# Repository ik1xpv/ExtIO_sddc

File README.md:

## ExtIO_sddc.dll (software digital down converter) - Oscar Steila, ik1xpv

## Installation Instructions

You can download the latest EXTIO driver from the releases: https://github.com/ik1xpv/ExtIO_sddc/releases.
The direct link to the current version v1.2.0 Version released at 18/3/2021 is: https://github.com/ik1xpv/ExtIO_sddc/releases/download/v1.2.0/SDDC_EXTIO.ZIP.

*If you want to try the beta EXTIO driver which is for testing, you can find the binary for each change here: https://github.com/ik1xpv/ExtIO_sddc/actions. Select one specific code change you like to try, click on the link of the change. And you will find the binary on the bottom of the change.*

## Build Instructions for ExtIO

1. Install Visual Studio 2019 with Visual C++ support. You can use the free community version, which can be downloaded from: https://visualstudio.microsoft.com/downloads/
1. Install CMake 3.19+, https://cmake.org/download/
1. Running the following commands in the root folder of the cloned repro:

```bash
> mkdir build
> cd build
> cmake ..
> cmake --build .
or
> cmake --build . --config Release
> cmake --build . --config RelWithDebInfo
```

* You need to download **32bit version** of fftw library from fftw website http://www.fftw.org/install/windows.html. Copy libfftw3f-3.dll from the downloaded zip package to the same folder of extio DLL.

* If you are running **64bit** OS, you need to run the following different commands instead of "cmake .." based on your Visual Studio Version:
```
VS2022: >cmake .. -G "Visual Studio 17 2022" -A Win32
VS2019: >cmake .. -G "Visual Studio 16 2019" -A Win32
VS2017: >cmake .. -G "Visual Studio 15 2017 Win32"
VS2015: >cmake .. -G "Visual Studio 14 2015 Win32"
```

## Build Instructions for firmware

- download latest Cypress EZ-USB FX3 SDK from here: https://www.cypress.com/documentation/software-and-drivers/ez-usb-fx3-software-development-kit
- follow the installation instructions in the PDF document 'Getting Started with FX3 SDK'; on Windows the default installation path will be 'C:\Program Files (x86)\Cypress\EZ-USB FX3 SDK\1.3' (see pages 17-18) - on Linux the installation path could be something like '/opt/Cypress/cyfx3sdk'
- add the following environment variables:
```
export FX3FWROOT=<installation path>
export ARMGCC_INSTALL_PATH=<ARM GCC installation path>
export ARMGCC_VERSION=4.8.1
```
(on Linux you may want to add those variables to your '.bash_profile' or '.profile')
- all the previous steps need to be done only once (or when you want to upgrade the version of the Cypress EZ-USB FX3 SDK)
- to compile the firmware run:
```
cd SDDC_FX3
make
```

## Build Instruction for Linux

1. Install development packages:
```bash
> sudo apt install libfftw3-dev
```

1. Follow Windows Build Instruction to run cmake to build Linux libaray

## Directory structure:
    \Core\           > Core logic of the component
        r2iq.cpp			> The logic to demodulize IQ from ADC real samples
        FX3handler.cpp		> Interface with firmware
        RadioHandler.cpp    > The abstraction of different radios
        Radio\*.cpp         > Hardware specific logic
    \ExtIO_sddc\ 		> ExtIO_sddc sources,
        extio_sddc.cpp     > The implementation of EXTIO contract 
        tdialog.cpp			> The Configuration GUI Dialog
    \libsddc\        > libsddc lib
    \SDDC_FX3\          > Firmware sources

## Change Logs

### tag v1.4 version date 7/5/2024
- Add SoapySDR module for Linux & Windoes
- Embedded firmware into Core to avoid carrying firmware file.

Install SoapySDR on Linux via the follow command:
> export SOAPY_SDR_PLUGIN_PATH=<path of libSDDCSupport.so>

### tag  v1.3.0RC1 Version "V1.2 RC1" date 4/11/2021
- Use Ringbuffer for input and output #157
- Delegate the VHF and HF decision to radio class #194
- Debug trace via USB #195
- Arm neon port #203
- A dialogBox with SDR name and FX3 serial number allows selection of a device from many. #210

 So far the known issues:
- Al power up sometime FX3 is not enumerated as Cypress USB FX3 BootLoader Device. When it happens also Cypress USB Control Center app is not able to detect it and a hardware disconnect and reconnect maybe required to enumerate the unit.

### tag  v1.2.0 Version "V1.2.0" date 18/3/2021
- Fix the crosstalk HF <-> VHF/UHF issue #177
- When HDSDR's version >= HDSDR v2.81 beta3 (March 8, 2021) following an ADC's sampling rate change the new IF bandwidths are computed dynamically and restart of HDSDR in not required.

### tag  v1.2RC1 Version "V1.2 RC1" date 18/2/2021
- The ADC's nominal sampling frequency is user selectable from 50 MHz to 140 MHz at 1Hz step, 
- The reference calibration can be adjusted in the dialog GUI in a range of +/- 200 ppm. (#171)
- The tuner IF center frequency is moved to 4.570 MHz that is the standard for RT820T. We were using 5 MHz before when we did not have yet fine tune ability. (#159)
- Support for AVX/2/512 instructions added. This change may reduce CPU usage for some modern hardware.(#152) 
- The Kaiser-Bessel IF filter with 85% of Nyquist band are computed at initialization. It simplifies managment of IF filters (#147)
- Add automatically build verification for both master branch and PRs. This  feature of the Github environment speeds development checks(#141)

 So far the known issues:
- The ADC sampling frequency can be selected via the ExtIO dialog.  HDSDR versions <= 2.80 require to close HDSDR.exe and restart the application to have the right IF sample rates. Higher HDSDR releases will have dynamically allocated IF sample rates and they will not require the restart.
- This release does not operate correctly with HF103 and similar designs that do not use a pll to generate the ADC sampling clock.
- The accuracy is that of the SI5351a programming about 1 Hz

### tag  v1.1.0 Version "V1.1.0" date 29/12/2020
- Fix the round of rf/if gains in the UI #109
- Fix sounds like clipping, on strong stations #120
- Fix reboot of FX3 #119

 So far the known issues:
- The reference frequency correction via HDSDR -> Options -> Calibration Settings ->LO Frequency Calibration doesn't work correctly. This problem will be addressed in the next release.

### tag  v1.1RC1 Version "V1.1 RC1" date 20/12/2020
- Supports 128M ADC sampling rate selectable via the dialog GUI ( Justin Peng and Howard Su )
- Use of libsddc allows development of Linux support and Soapy integration ( Franco Venturi https://github.com/fventuri/libsdd) 
- Tune the LO with a 1Hz step everywhere (Hayati Ayguen https://github.com/hayguen/pffft).
- Move multi thread r2iq to a multithreaded pipeline model to better leverage multi cores. Remove callback in USB (adcsample) thread to HDSDR to make sure we can reach 128Msps.
- Continuous tuning LW,MW,HF and VHF.
- Dialog GUI has samplerates and gains settings for use with other SDR applications than HDSDR.
- Test harmonic R820T tuning is there (Hayati Ayguen https://github.com/librtlsdr/librtlsdr/tree/development)
- the gain correction is made via  HDSDR -> Options -> Calibration Settings ->S-Meter Calibration.

 So far the known issues:
- The reference frequency correction via HDSDR -> Options -> Calibration Settings ->LO Frequency Calibration doesn't work correctly. This problem will be addressed in the next release.
- The 128M adc rate is experimental and must be activated manually in the ExtIO dialog GUI. It works with RX888 hardware that have 60 MHz LPF and requires a quite fast PC.

### tag  v1.01 Version "V1.01 RC1" date 06/11/2020
- SDDC_FX3 directory contains ARM sources and GPIFII project to compile sddc_fx3.img
- Detects the HW type: BBRF103, BBRF103, RX888 at runtime.
- Si5351a and R820T2 driver moved to FX3 code
- Redesign of FX3 control commands
- Rename of FX3handler (ex: OpenFX3) and RadioHandler (ex: BBRF103) modules
- Simplified ExtIO GUI Antenna BiasT, Dither, and Rand.
- Reference frequency correction via software +/- 200 ppm range
- Gain adjust +/-20 dB step 1dB
- R820T2 controls RF gains via a single control from GUI
- ExtIO.dll designed for HDSDR use.
- HF103 added a tuning limit at ADC_FREQ/2.

### tag  v0.98  Version "SDDC-0.98" date  13/06/2019
   R820T2 is enabled to support VHF

### tag  v0.96  Version "SDDC-0.96" date  25/02/2018

### tag  v0.95  Version "SDDC-0.95" date 31/08/2017

Initial version

## References
- EXTIO Specification from http://www.sdradio.eu/weaksignals/bin/Winrad_Extio.pdf
- Discussion and Support https://groups.io/g/NextGenSDRs
- Recommended Application http://www.weaksignals.com/
- http://www.hdsdr.de
- http://booyasdr.sourceforge.net/
- http://www.cypress.com/

## Many thanks to
- Alberto di Bene, I2PHD
- Mario Taeubel
- LightCoder (aka LC)
- Howard Su
- Hayati Ayguen
- Franco Venturi
- All the Others !

#### 2016,2017,2018,2019,2020,2021  IK1XPV Oscar Steila - ik1xpv(at)gmail.com
https://sdr-prototypes.blogspot.com/

http://www.steila.com/blog

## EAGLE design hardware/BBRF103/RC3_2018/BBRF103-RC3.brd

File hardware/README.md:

## Hardware related documents

.Todo..

## Directory structure:
    \BBRF103\           
		RC1_2017\	> by Oscar Steila
		RC2_2018\	> by Oscar Steila
       	RC3_2018\	> by Radek Haša
		
	\RF103			> by Oscar Steila 
	
	\RX888			> by Justin Peng and Howard Su
	
	\Filters\
		2m_PBF_rev1.zip	> pcb gerbers see https://sdr-prototypes.blogspot.com/2021/03/filter-in-box.html

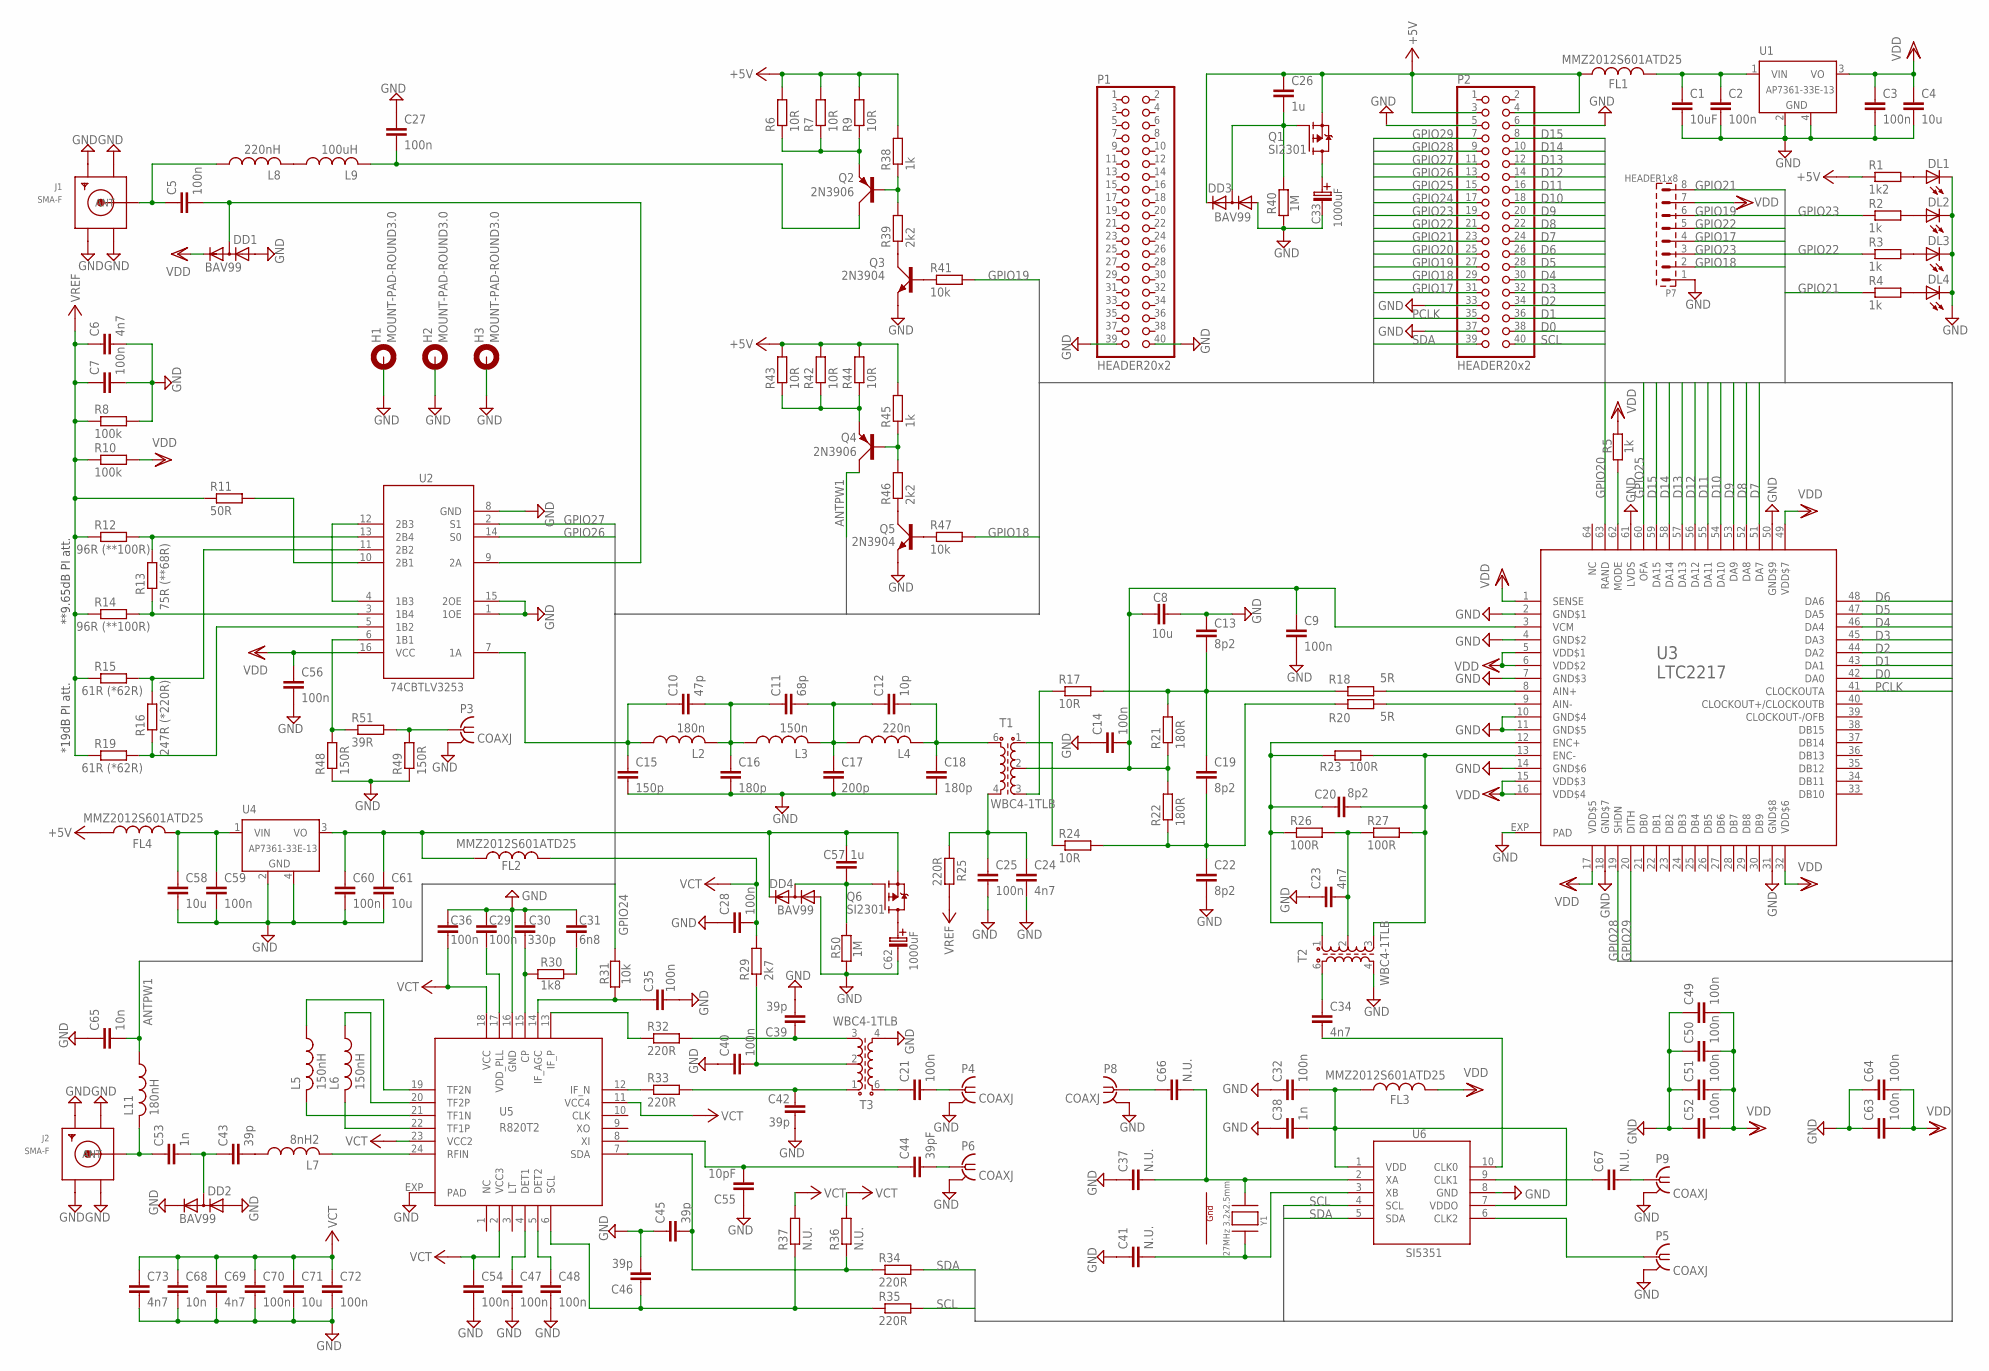
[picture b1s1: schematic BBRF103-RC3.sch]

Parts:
C1: 10uF; C0805K
C2, C3, C5, C7, C9, C14, C21, C25, C27, C28, C29, C32, C35, C36, C40, C47, C48, C49, C50, C51, C52, C54, C56, C59, C60, C63, C64, C70, C72: 100n; C0603K
C4, C58, C61, C71: 10u; C0805K
C6, C23, C24, C34, C69, C73: 4n7; C0603K
C8: 10u; C0603K
C10: 47p; C0603K
C11: 68p; C0603K
C12: 10p; C0603K
C13, C19, C20, C22: 8p2; C0603K
C15: 150p; C0603K
C16, C18: 180p; C0603K
C17: 200p; C0603K
C26, C57: 1u; C0603K
C30: 330p; C0603K
C31: 6n8; C0603K
C33, C62: 1000uF; C_EL_5
C37, C41, C66, C67: N.U.; C0603K
C38, C53: 1n; C0603K
C39, C42, C43, C45, C46: 39p; C0603K
C44: 39pF; C0603K
C55: 10pF; C0603K
C65, C68: 10n; C0603K
DD1, DD2, DD3, DD4: BAV99; SOT23
DL1, DL2, DL3, DL4: LEDCHIPLED_0805; CHIPLED_0805
FL1, FL2, FL3, FL4: MMZ2012S601ATD25; L2012C
H1, H2, H3: MOUNT-PAD-ROUND3.0; 3,0-PAD
J1, J2: SMA-F; SMA_EDGELAUNCH
L2: 180n; L2012C
L3: 150n; L2012C
L4: 220n; L2012C
L5, L6: 150nH; C0603K
L7: 8nH2; C0603K
L8: 220nH; L2012C
L9: 100uH; L2012C
L11: 180nH; C0603K
P1, P2: HEADER20x2; 2X20
P3, P4, P5, P6, P8, P9: COAXJ
P7: HEADER1x8; S1G8_JUM
Q1, Q6: SI2301; SOT23
Q2, Q4: 2N3906; SOT23W_INFINEON
Q3, Q5: 2N3904; SOT23W_INFINEON
R1: 1k2; R0603
R2, R3, R4, R5, R38, R45: 1k; R0603
R6, R7, R9, R17, R24, R42, R43, R44: 10R; R0603
R8, R10: 100k; R0603
R11: 50R; R0603
R12, R14: 96R (**100R); R0603
R13: 75R (**68R); R0603
R15, R19: 61R (*62R); R0603
R16: 247R (*220R); R0603
R18, R20: 5R; R0603
R21, R22: 180R; R0603
R23, R26, R27: 100R; R0603
R25, R32, R33, R34, R35: 220R; R0603
R29: 2k7; R0603
R30: 1k8; R0603
R31, R41, R47: 10k; R0603
R36, R37: N.U.; R0603
R39, R46: 2k2; R0603
R40, R50: 1M; R0603
R48, R49: 150R; R0603
R51: 39R; R0603
T1, T2, T3: WBC4-1TLB; WBC4-1WL
U1, U4: AP7361-33E-13; SOT223
U2: 74CBTLV3253; TSSOP16
U3: LTC2217; QFN64-9X9
U5: R820T2; QFN24
U6: SI5351; MSOP10
Y1: 27MHz 3.2x2.5mm; NX3225

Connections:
+5V: C26.1, DD3.2 (C), FL1.1, FL4.1, P2.3, P2.4, Q1.2 (S), R1.1, R6.2, R7.2, R9.2, R38.2, R42.2, R43.2, R44.2, R45.2
ANTPW1: C65.2, L11.1, Q4.3 (C)
D0: P2.38, U3.42 (DA0)
D1: P2.36, U3.43 (DA1)
D2: P2.34, U3.44 (DA2)
D3: P2.32, U3.45 (DA3)
D4: P2.30, U3.46 (DA4)
D5: P2.28, U3.47 (DA5)
D6: P2.26, U3.48 (DA6)
D7: P2.24, U3.51 (DA7)
D8: P2.22, U3.52 (DA8)
D9: P2.20, U3.53 (DA9)
D10: P2.18, U3.54 (DA10)
D11: P2.16, U3.55 (DA11)
D12: P2.14, U3.56 (DA12)
D13: P2.12, U3.57 (DA13)
D14: P2.10, U3.58 (DA14)
D15: P2.8, U3.59 (DA15)
G1: Y1.4 (G1)
G2: Y1.2 (G2)
GND: C1.2, C2.2, C3.2, C4.2, C6.2, C7.2, C8.2, C9.2, C13.1, C14.1, C15.2, C16.2, C17.2, C18.2, C22.2, C23.1, C24.2, C25.2, C27.1, C28.1, C29.1, C30.1, C31.1, C32.1, C33.C- (C_EL-), C35.2, C36.1, C37.1, C38.1, C39.2, C40.1, C41.1, C42.1, C45.1, C46.2, C47.2, C48.2, C49.1, C50.1, C51.1, C52.1, C54.2, C55.1, C56.2, C58.2, C59.2, C60.2, C61.2, C62.C- (C_EL-), C63.1, C64.1, C65.1, C68.2, C69.2, C70.2, C71.2, C72.2, C73.2, DD1.1 (A), DD2.1 (A), DD2.2 (C), DD3.1 (A), DD4.1 (A), DL1.C, DL2.C, DL3.C, DL4.C, H1.B3,0, H2.B3,0, H3.B3,0, J1.GND@1 (GND4), J1.GND@2 (GND3), J1.GND@3 (GND2), J1.GND@4 (GND1), J2.GND@1 (GND4), J2.GND@2 (GND3), J2.GND@3 (GND2), J2.GND@4 (GND1), P1.39, P1.40, P2.5, P2.6, P2.33, P2.37, P3.2 (GND), P4.2 (GND), P5.2 (GND), P6.2 (GND), P7.1, P8.2 (GND), P9.2 (GND), Q3.2 (E), Q5.2 (E), R8.2, R40.1, R48.1, R49.1, R50.1, T2.4, T3.4, U1.2 (GND), U1.4 (GND), U2.1 (1OE), U2.8 (GND), U2.15 (2OE), U3.2 (GND$1), U3.4 (GND$2), U3.7 (GND$3), U3.10 (GND$4), U3.11 (GND$5), U3.14 (GND$6), U3.18 (GND$7), U3.31 (GND$8), U3.50 (GND$9), U3.61 (LVDS), U3.EXP (PAD), U4.2 (GND), U4.4 (GND), U5.16 (GND), U5.EXP (PAD), U6.8 (GND)
GPIO17: P2.31, P7.4
GPIO18: P2.29, P7.2, R47.2
GPIO19: P2.27, P7.6, R41.2
GPIO20: P2.25, U3.63 (RAND)
GPIO21: P2.23, P7.8, R4.1
GPIO22: P2.21, P7.5, R3.1
GPIO23: P2.19, P7.3, R2.1
GPIO24: P2.17, R31.2
GPIO25: P2.15, U3.60 (OFA)
GPIO26: P2.13, U2.14 (S0)
GPIO27: P2.11, U2.2 (S1)
GPIO28: P2.9, U3.19 (SHDN)
GPIO29: P2.7, U3.20 (DITH)
unnamed: DL1.A, R1.2
unnamed: C33.C+ (C_EL+), Q1.3 (D)
unnamed: C26.2, DD3.3 (AC), Q1.1 (G), R40.2
unnamed: DL2.A, R2.2
unnamed: DL3.A, R3.2
unnamed: DL4.A, R4.2
unnamed: R5.1, U3.62 (MODE)
unnamed: C20.2, R23.2, R27.2, T2.3, U3.13 (ENC-)
unnamed: C1.1, C2.1, FL1.2, U1.1 (VIN)
unnamed: C23.2, R26.2, R27.1, T2.2
unnamed: C20.1, R23.1, R26.1, T2.1, U3.12 (ENC+)
unnamed: C34.1, T2.6
unnamed: C34.2, U6.10 (CLK0)
unnamed: C37.2, C66.2, U6.2 (XA), Y1.1 (X1)
unnamed: C67.2, P9.1
unnamed: C66.1, P8.1
unnamed: C32.2, C38.2, FL3.1, U6.1 (VDD), U6.7 (VDDO)
unnamed: C67.1, U6.9 (CLK1)
unnamed: P5.1, U6.6 (CLK2)
unnamed: R20.2, U3.9 (AIN-)
unnamed: R18.2, U3.8 (AIN+)
unnamed: C41.2, U6.3 (XB), Y1.3 (X2)
unnamed: C13.2, C19.1, R17.2, R18.1, R21.2
unnamed: C8.1, C9.1, C14.2, R21.1, R22.2, T1.2, U3.3 (VCM)
unnamed: C19.2, C22.1, R20.1, R22.1, R24.2
unnamed: R24.1, T1.1
unnamed: R17.1, T1.3
unnamed: C24.1, C25.1, R25.1, T1.4
unnamed: C12.2, C18.1, L4.2, T1.6
unnamed: C11.2, C12.1, C17.1, L3.2, L4.1
unnamed: C10.2, C11.1, C16.1, L2.2, L3.1
unnamed: C10.1, C15.1, L2.1, U2.7 (1A)
unnamed: C62.C+ (C_EL+), Q6.3 (D)
unnamed: Q3.1 (B), R41.1
unnamed: Q3.3 (C), R39.1
unnamed: Q2.1 (B), R38.1, R39.2
unnamed: C58.1, C59.1, FL4.2, U4.1 (VIN)
unnamed: C57.2, DD4.3 (AC), Q6.1 (G), R50.2
unnamed: Q2.2 (E), R6.1, R7.1, R9.1
unnamed: C48.1, U5.5 (DET2)
unnamed: C45.2, R34.1, R36.1, U5.7 (SDA)
unnamed: Q5.1 (B), R47.1
unnamed: Q5.3 (C), R46.1
unnamed: Q4.1 (B), R45.1, R46.2
unnamed: Q4.2 (E), R42.1, R43.1, R44.1
unnamed: C47.1, U5.4 (DET1)
unnamed: C21.1, T3.6
unnamed: C21.2, P4.1
unnamed: C42.2, R33.2, T3.1
unnamed: C39.1, R32.2, T3.3
unnamed: C40.2, R29.1, T3.2
unnamed: R48.2, R51.1, U2.6 (1B1)
unnamed: R33.1, U5.12 (IF_N)
unnamed: C44.2, P6.1
unnamed: C44.1, C55.2, U5.8 (XI)
unnamed: C46.1, R35.1, R37.1, U5.6 (SCL)
unnamed: P3.1, R49.2, R51.2
unnamed: R32.1, U5.13 (IF_P)
unnamed: C35.1, R31.1, U5.14 (IF_AGC)
unnamed: C30.2, R30.1, U5.15 (CP)
unnamed: C31.2, R30.2
unnamed: C27.2, L9.2, Q2.3 (C)
unnamed: C29.2, U5.17 (VDD_PLL)
unnamed: C5.2, DD1.3 (AC), U2.9 (2A)
unnamed: L8.2, L9.1
unnamed: L6.2, U5.22 (TF1P)
unnamed: L6.1, U5.20 (TF2P)
unnamed: L5.2, U5.21 (TF1N)
unnamed: L5.1, U5.19 (TF2N)
unnamed: L7.2, U5.24 (RFIN)
unnamed: C43.2, L7.1
unnamed: C43.1, C53.2, DD2.3 (AC)
unnamed: C5.1, J1.P (ANT), L8.1
unnamed: C53.1, J2.P (ANT), L11.2
unnamed: R12.2, R13.2, U2.13 (2B4)
unnamed: C57.1, C60.1, C61.1, DD4.2 (C), FL2.1, Q6.2 (S), U4.3 (VO)
unnamed: R13.1, R14.2, U2.3 (1B4)
unnamed: R15.2, R16.2, U2.11 (2B2)
unnamed: R16.1, R19.2, U2.5 (1B2)
unnamed: U2.4 (1B3), U2.12 (2B3)
unnamed: R11.2, U2.10 (2B1)
PCLK: P2.35, U3.41 (CLOCKOUTA)
SCL: P2.40, R35.2, U6.4 (SCL)
SDA: P2.39, R34.2, U6.5 (SDA)
VCT: C28.2, C36.2, C54.1, C68.1, C69.1, C70.1, C71.1, C72.1, C73.1, FL2.2, R29.2, R36.2, R37.2, U5.2 (VCC3), U5.11 (VCC4), U5.18 (VCC), U5.23 (VCC2)
VDD: C3.1, C4.1, C49.2, C50.2, C51.2, C52.2, C56.1, C63.2, C64.2, DD1.2 (C), FL3.2, P7.7, R5.2, R10.2, U1.3 (VO), U2.16 (VCC), U3.1 (SENSE), U3.5 (VDD$1), U3.6 (VDD$2), U3.15 (VDD$3), U3.16 (VDD$4), U3.17 (VDD$5), U3.32 (VDD$6), U3.49 (VDD$7)
VREF: C6.1, C7.1, R8.1, R10.1, R11.1, R12.1, R14.1, R15.1, R19.1, R25.2

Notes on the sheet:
*19dB PI att.
**9.65dB PI att.

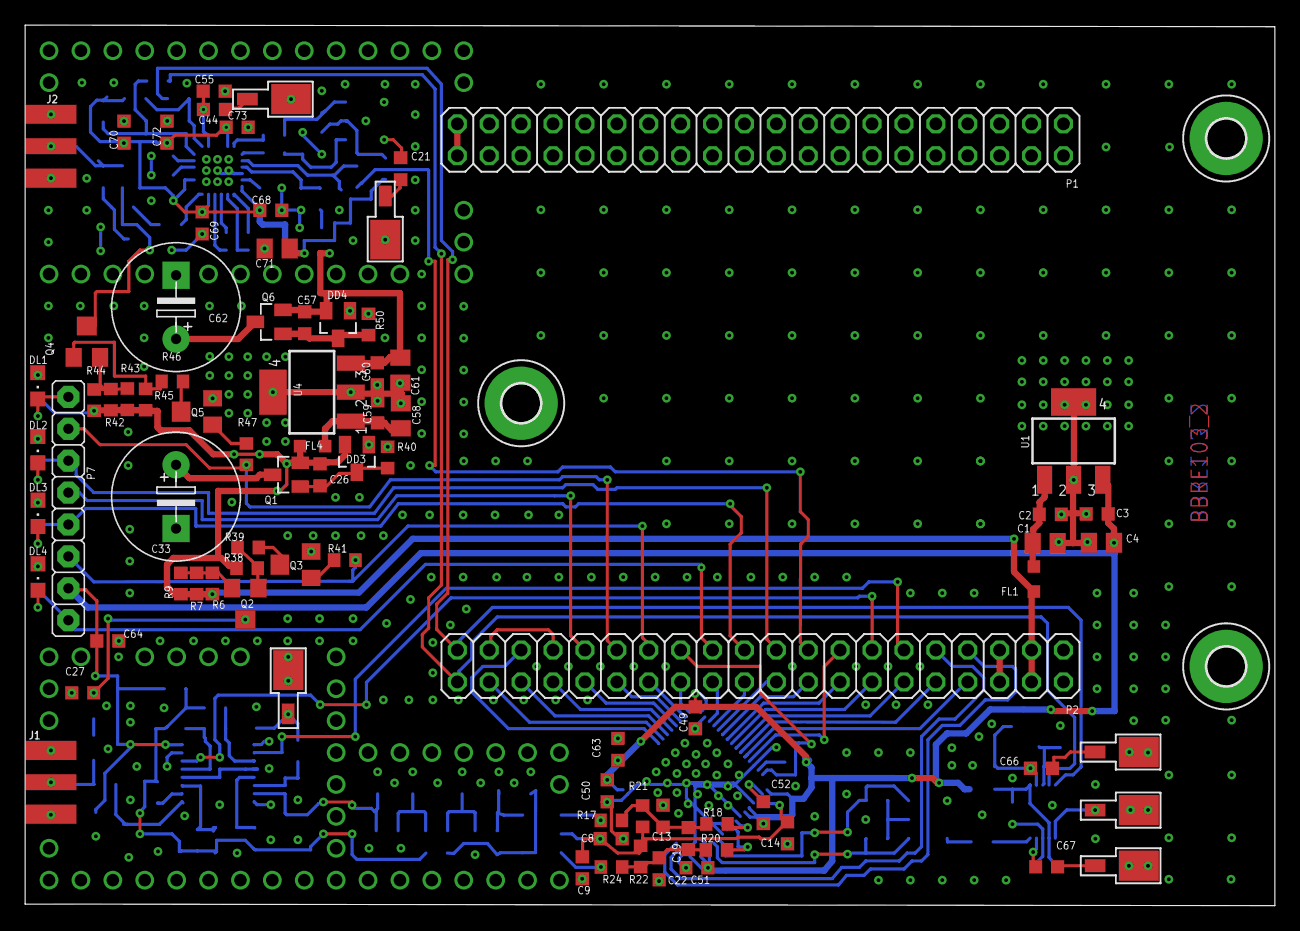
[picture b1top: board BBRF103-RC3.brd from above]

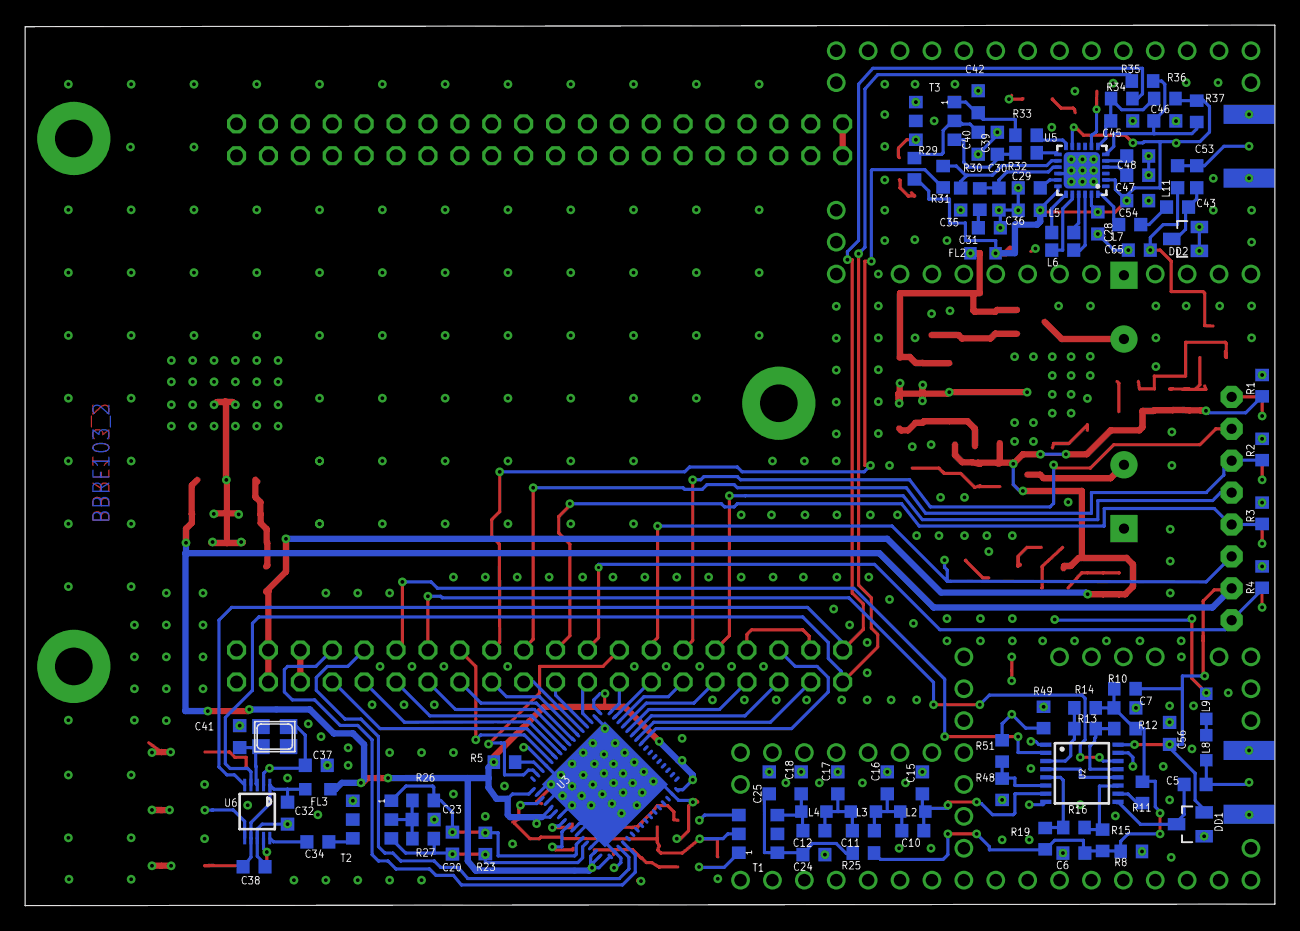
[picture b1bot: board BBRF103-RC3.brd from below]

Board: 2 copper layers, 99.5 x 70.1 mm, 174 parts (88 on the bottom side), 119 nets.

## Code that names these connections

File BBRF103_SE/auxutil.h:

#ifndef _INCLUDED_AUXUTIL_H_
#define _INCLUDED_AUXUTIL_H_

#include "cyu3externcstart.h"
//#include "cyu3types.h"
#include "cyu3usbconst.h"
#include "cyu3usb.h"

#define LED_OVERLOAD (21)
#define LED_MODEA    (22)
#define LED_MODEB    (23)
// redefine to error handler
#define GPIO_LED1   (21)
#define GPIO_LED2   (22)
#define GPIO_LED3   (23)
#define LED_ON (1)
#define LED_OFF (0)
#define ERR_DIGIT_ON	100
#define ERR_DIGIT_OFF	400
#define ERR_DIGIT_SPACE	250
#define ERR_DIGIT_END   750

#define OUTXIO0 (1) 	// LED_OVERLOAD  GPIO21  bit position
#define OUTXIO1 (2) 	// LED_MODEA  GPIO22
#define OUTXIO2 (4) 	// LED_MODEB  GPIO22

#define OUTXIO3 (8)  	// SEL0  GPIO26
#define OUTXIO4 (16) 	// SEL1  GPIO27

#define OUTXIO5 (32)  	// SHDWN  GPIO28
#define OUTXIO6 (64)  	// DITH   GPIO29
#define OUTXIO7 (128)  	// DITH   GPIO20

typedef struct outxio_t
{
    uint8_t  buffer[4];         /* The actual byte used is [0]  */
} outxio_t;

typedef struct i2cxio_t
{
    uint8_t  i2caddr;            /* The i2c device address  */
    uint8_t  regaddr;            /* The device register address  */
    uint8_t  isRead;           	 /* (0) False value WRITE, (1) True value Read */
    uint8_t  lencount;			 /*	 byte count  < 12 */
    uint8_t  databyte[12];
} i2cxio_t;


#define CY_FX_RQT_I2C_WRITE                     (0xBA)
#define CY_FX_RQT_I2C_READ                      (0xBE)
#define CY_FX_RQT_GPIO_WRITE 					(0xBC)
#define CY_FX_RQT_GPIO_PWM                      (0xBD)
#define CY_FX_RQT_RESET                      	(0xCC)
#define CY_FX_RQT_START                      	(0xAA)
#define CY_FX_RQT_STOP                      	(0xBB)

void CyFxAppErrorHandler (  CyU3PReturnStatus_t apiRetStatus );
CyBool_t CyFxApplnLPMRqtCB ( CyU3PUsbLinkPowerMode link_mode);
void CyFxSlFifoApplnDebugInit (void);
void setDescriptors(void);
void SDR_ErrorHandler( CyU3PReturnStatus_t apiRetStatus, int code );
#endif

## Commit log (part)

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2021-03-17 Fix cross lock issue (#183)
    * Always stop r820 no matter if init is done
    * Add delay before checking PLL lock state
2021-03-17 New way to upload artifact
2021-03-17 New way to upload artifact (#184)
2021-03-18 restructure the source code
2021-03-18 Add FX3 SDK
2021-03-18 Add action support to build firmware
2021-03-18 Use the proper config
2021-03-18 seperate the firmware build
2021-03-18 fix build again
2021-03-18 Move declare to header file
2021-03-18 use firmware from linux build
2021-03-18 fix the build type constant
2021-03-18 v1.2.0 candidate (#185)
    Label v1.2.0 change
2021-03-18 Update RadioHandler.cpp
    VHF tuning sign of correction fixed
2021-03-18 Update RadioHandler.cpp (#186)
    VHF tuning sign of correction fixed
2021-03-19 Reduce cross talk from HF->VHF (#187)
2021-03-22 Update RX888R2Radio.cpp (#189)
2021-03-22 serial trace fix 4
2021-03-23 serial trace fix 4 (#190)
    * serial trace fix 4
    * layout fix
2021-03-25 Add libusb support
2021-03-27 Update README.md (#192)
2021-04-04 RXLUCY fix 2
2021-04-11 Fix build on OSX
2021-04-11 Move rf mode switching into hardware
2021-04-11 normalize tuner interface
2021-04-11 Cleanup ad5815 driver
2021-04-11 Add FM Notch
2021-04-11 Add prototype
2021-04-11 update rx888r3
2021-04-11 Fix linux build
2021-04-12 Add undersampling support
2021-04-12 Fix tune logic
2021-04-13 Fix tuner
2021-04-13 Debug trace FX3 via USB
2021-04-14 Reload FX3 linuxFix
2021-04-14 Debug trace FX3 via USB (#195)
    * Debug trace FX3 via USB
    * Reload FX3 linuxFix
    * linux fix tentative 2
2021-04-14 Update driver
2021-04-14 Fix gpio set for rx888r3
2021-04-15 Move to IF=20M
2021-04-15 Fix a number typo
2021-04-17 fix step 3
2021-04-18 Lower the switch point to 220M
2021-04-19 selection USB UART console
    define _DEBUG_USB_ in Interface.h
    ifdef USB <-> ExtIO dialog console
    else UART <-> serial terminal
2021-04-19 command list fix
2021-04-19 maxlen fix
    MAXLEN_D_USB is defined in Interface,h
2021-04-20 Move rf mode switching into hardware (#194)
    Delegate the VHF and HF decision to radio class.
    Normalize Tuner logic inside firmware. No matter what tuner is used, the interface kept same.
    add rx888mk3 prototype code.
2021-04-20 Update to 194
    _DEBUG flag is commented in config,h
    defined in project configuration debug
    In rd5815 is used DebugPrinf that can be definad as USB or serial in Application.h
2021-04-20 Console input2 fx3 (#197)
    * fix step 3
    * selection USB UART console
    define _DEBUG_USB_ in Interface.h
    ifdef USB <-> ExtIO dialog console
    else UART <-> serial terminal
    * fix Enter command
2021-04-24 GPIO50 pd BBRF103 (#198)
    BBRF103 detects pull down at GPIO50
2021-04-26 Remove inputbuffer parameter
2021-04-26 Move out simd related functions to simd.h
2021-04-26 Move plan_f2t out of thread context
2021-04-26 reduce spin count to 100
2021-04-27 Use Ringbuffer for Input&output Buffer (#157)
    * use Ringbuffer for input and output
    * Still use fixed EXT_BLOCKLEN
    * Fix Linux build
    * Fix linux build
    * reduce spin count to 100
2021-04-27 reformat the code a bit
2021-04-29 fix noise issue
2021-04-30 Create ifft plan once
2021-04-30 Support more decimate rates
2021-05-06 Use Start function to pass adcrate
2021-05-06 fix tune frequency logic
2021-05-06 Fix test case
2021-05-06 Fix libsddc on new API
2021-05-06 Get ExtIO works under new code
2021-05-06 Add back the support to save samples
2021-05-10 EXT_BLOCKLEN is parameter of freq2iq.
2021-05-10 Add back the debug and stats support
2021-05-10 Move intitialize to constructor
2021-05-10 remove debug code
2021-05-11 Add new interface to get uniqe serial number
2021-05-14 Cleanup the code
2021-05-28 Fix the size issue for ringbuffer
2021-07-15 Dynamic detection of NEON from hardware
2021-07-15 Compiles and passes unit tests on ARMv7 (OrangePi)
2021-07-15 X86_64 testing, portable printf format
2021-07-15 Return to 1 second run time for R2IQ tests
2021-09-29 Arm neon port (#203)
    * Compiles and passes unit tests on ARMv7 (OrangePi)
    * Dynamic detection of NEON from hardware
    * Rate limit hardware emulator, print counters
    * X86_64 testing, portable printf format
    * Return to 1 second run time for R2IQ tests
    * Remove wisdom files, align printf
2021-09-29 Detect RX888 more reliable (#204)
2021-10-24 two devices manual selection
    If the fx3handler::GetFx3Device() finds two devices a msgBox at run time asks witch one use.
    It's a rude solution , a better one with the use of SN to identify the device is planned in future
2021-10-27 Update FX3handler.cpp
    Message Box label
2021-10-29 Wait after firmware change
    If the device at power up is detected as Cypress FX3 Bootloader device,
    the added wait gives more time to enumering as StreamerExample device
2021-11-03 Select dialogbox
    In ExtIO_sddc,cpp InitHW() opens dialogBox to select a device when there are many FX3 devices.
2021-11-03 Linux build patch
    TODO
2021-11-03 linux buils hoops
2021-11-04 Ver 1.3.0 RC1 FW 2.02
    SWVERSION 1.3.0 RC1
    Firmware 2.02
2021-11-04 two devices manual selection (#210)
    * in the USBdescriptor of FX3 the serial number has been added ( thanks to Franco ideas and code )
    * Ver 1.3.0 RC1 FW 2.02
    ExtIO_sddc enumerates all the Cypress FX3 connected devices.
    A dialogBox ask to select one of many if required.
2021-11-16 Fix the logic to detect HDSDR
2021-12-10 BBRF103 documentation update
    Old Posts added in \hardware\BBRF103
2021-12-12 Add logic to persistent settings in non-HDSDR (#205)
    * Add logic to persistent settings in non-HDSDR
    * Fix the logic to detect HDSDR
2022-03-08 Use windows-2019
    windows-latest doesn't carry vs2019
2022-03-08 Use windows-2019 (#215)
    windows-latest doesn't carry vs2019
2022-04-02 Fix for systems that do not support usbfs zerocopy feature.
2022-04-02 Fix compiler error with clang
2022-04-02 Fix compile error
2022-04-03 Improve internal API (#218)
    * Improve internal API
    * Fix Linux build
2022-04-11 Support multi channels in dsp
2022-04-13 Add hermeslite emu
2022-04-13 cleanup code
2022-04-13 Fix bug in multi channel
2022-05-08 Fix freq shift
2022-05-08 ringbuffer add timeout to prevent hang forever
2022-05-09 Support multi devices
2022-05-09 Cleanup
2022-05-10 Add const modifier to firmware array
    As the firmware BLOB is not expected to be changed during downloading to
    a device.
2022-05-10 another try to fix windows build
2022-05-10 Add const modifier to firmware array (#224)
    As the firmware BLOB is not expected to be changed during downloading to
    a device.
2022-05-10 Make it work under linux with gqrx/gr-osmosdr
    Requires patched gr-osmosdr (gr3.7 only so far)
    https://github.com/vladisslav2011/gr-osmosdr/tree/ngrx
    No correct device listing and sample rates list.
    Gain selection is still a bit buggy.
    Fix test segfault.
    Do not delete fx3Handler as RadioHandlerClass::~RadioHandlerClass()
2022-05-10 Upload new firmware
2022-05-10 Improve compatibility with intel hubs (#225)
    Disable LPM while streaming to prevent dropouts.
2022-05-10 One more place to use const for firmware binary (#226)
2022-05-11 Use sampling rate of 96M
2022-05-15 define ht lenght
    #define HTLEN in fft_mt_r2iq.cpp allows manual test other lenght
2022-05-16 HTLEN
    #define HTLEN in config.h
2022-05-21 Soft tone generator
    #define _SOFT_TONE_DEBUG in config.h
    enables the generation of soft tone
    close to 1MHz with ADC clk 64MHz,
    the tone period is an integer factor of transferSamples.
    GUI Rand CheckBox activates the software generated tone.
2022-05-23 Update config.h
    SWVERSION 1.3.3.Alfa
2022-06-09 large FFTN test
    Test in config,c FFTN_R_ADC (32768)
    htlen => 12289
2022-09-03 Include git version tag into the version number
2022-09-03 Add dev index to open API of core
2022-09-03 Embed firmware file into libsddc
2022-09-05 Add error codes
2022-09-05 Cleanup CMakeLists.txt
2022-09-05 Include git version tag into the version number (#228)
2023-10-29 Do not build linux support on windows machine
2023-10-30 Start refactoring to add libusb support in windows
2023-10-30 Save wip
2023-10-31 Fix some some msvc compile warnings
2023-11-02 Refactor large part of code and dir structures
2023-11-02 Fix CyAPI support build
2023-11-02 Try to fix libusb support build
2023-11-02 Fix optimisation warnings
2023-11-02 Use safe functions and fix some warnings
2023-11-03 Fix libusb include error
2023-11-03 Fix libusb include on macOS
2023-11-04 Windows : Integrate CyAPI and libusb support in one static libUsb library
2023-11-04 Fix build in windows
2023-11-05 Fix unit tests build
2023-11-06 Refactor more wip
2023-11-06 Fix unittest build on windows
2023-11-08 Cmake : Clean some lines
2023-11-10 Convert a function that translates wide characters to multibyte characters from Windows-specific code to multiplatform code
2023-11-26 Fix compiling in mingw64
2023-11-30 Try to fix build in mingw64
2023-12-03 fix macos build
2023-12-06 Fix parallel build
2023-12-07 Clean
2023-12-07 Clean code
2023-12-19 Spectrum works in gqrx
2023-12-22 Fix build in mingw
2023-12-24 Use CyAPI driver by default
2023-12-25 Soapy : Add getFrequency method
2023-12-25 Some progression in frequency control
2023-12-29 Fix build in linux
2024-01-04 Fix build on ubuntu 18.04
2024-01-07 Fix unittest
2024-01-09 Fix firmware build
2024-01-11 Fix firmware build (#232)
2024-01-11 Fix linux build for UT (#233)
2024-01-14 Fix SoapySDRUtil --probe command
2024-01-14 Fix some memory leaks
2024-07-03 getName is a const function
2024-07-03 Add prefix to debug output
2024-07-04 initialize block_size
2024-07-04 add debug options
2024-07-04 SOAPYSDR lib works
2024-07-05 revert the change to clearnup transfer
2024-07-06 Fix usb handling
2024-07-06 更新 FX3handler.cpp
    fix windows build
2024-07-06 Add frequency list
2024-07-06 Support Gain modes
2024-07-06 Unroll some tight loops
2024-07-06 Fix UT
2024-07-08 cleanup cmakefiles
2024-07-08 Fix compile under x64
2024-07-08 frequency is uint64
2024-07-09 Fix USB Crash
    developed by Franco VENTURI
2024-07-09 Fix github action to add 64bit build and soapy build
2024-07-12 Update vcpkg
2024-07-12 Use vcpkg for win64 build
2024-07-12 add SoapySDR Lib (#234)
    * getName is a const function
    * Add prefix to debug output
    * Add SoapySDR lib named sddc
    * initialize block_size
    * add debug options
    * SOAPYSDR lib works
2024-07-19 Make streaming work in macos(intel)
2024-07-19 Fix hang issue when stopping stream
2024-08-24 Github actions: Add macos CI
2025-04-16 Allow toggle bias-t in SoapySDDC
2025-04-26 check boolen value safer
2025-04-26 Allow toggle bias-t in SoapySDDC (#237)
    * Allow toggle bias-t in SoapySDDC
    * check boolen value safer
2025-04-26 Fix unittest compile failure
2025-11-01 Fix os
2025-11-01 Fix macos build for arm64
2025-11-01 Update filename
2025-11-01 Update vs version
2025-11-01 Update file upload path
2026-02-10 Fix frequency offset bug at 32MHz sample rate
    Remove hardcoded 8MHz offset in getFrequency() when sampleRate is 32MHz.
    This offset caused spectrum display to start at 8MHz instead of 0Hz,
    leaving 0-8MHz range empty.
    The bug existed since the initial SoapySDR implementation.
2026-02-11 Fix CI build: add apt-get update before package installation
2026-02-11 Fix PR #240 AI review comments: improve sample rate handling and error safety
    Addresses 5 of 6 AI code review comments on PR #240:
    1. **Comment #1 (Performance)**: Cache supportsHighADCFrequency() result in
    getSettingInfo() to avoid redundant calls.
    2. **Comment #2 (CRITICAL - Uninitialized variable)**: Initialize samplerateidx
    in constructor to match default sampleRate=32MHz. Previously undefined behavior
    if activateStream() called before setSampleRate().
2026-04-19 fix: issue-219
    Match the cmake system processor for the linux/arm64 platform

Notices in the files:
parts and their libraries:
Copyright (C) PaJa 2003-2009
Copyright (C) PaJa 2011-2014
Copyright (C) PaJa 2001-2014
